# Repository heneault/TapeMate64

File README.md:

# TapeMate64 - Connect your Commodore Datasette to a PC

**TapeMate64** is a compact and affordable USB adapter that lets you connect a **Commodore Datasette** to your PC via **USB** for both reading and writing cassette data. It enables you to **digitize original tapes** for archiving or for use in an emulator—without needing a working Commodore 64.

It also allows you to **write TAP images back to real cassette tapes**, so you can enjoy software on original hardware for the full retro experience.

---

## 📺 Project Presentation
Watch the full presentation and live demo of **TapeMate64** at the **TPUG (Toronto PET Users Group)** meeting (December 2025):

👉 **[TapeMate64 Presentation at TPUG - Watch on YouTube](https://youtu.be/ml87w1ATcyY?si=blFYjihloHmHbtkc)**

---

Based on the [TapeBuddy64](https://github.com/wagiminator/C64-Collection/tree/master/C64_TapeBuddy64) project, TapeMate64 adds a builder-friendly design. You can operate it via a command-line interface or a Python-based graphical front-end.

The main differences of TapeMate64 over the original TapeBuddy64 project are:

* It uses readily available and popular modules that are easy to order online, such as the **Arduino Nano Super Mini** and the **MT3608** boost converter.
* All modules and components are soldered using **Through-Hole Technology (THT)**, which is much simpler to solder than Surface-Mount Device (SMD) components.
* The original TapeBuddy code was **ported to the ATmega** microcontroller used by the Arduino board, which is a much more common CPU than the original.
* The software was also modified to provide **better precision** for long and short pulses.
* Enhanced CRC computation has been added for improved data integrity.
* The applications (GUI and command-line) are precompiled and ready to use, so there is no need to install Python.
* No switch is required for programming or operation, everything is handled automatically.
* Additional special-case handling was implemented, particularly for tape-writing operations.

__
__

---

# Where to Order a Kit

I will have some kits for sale at the [World of Commodore](https://woc.tpug.ca/) event, organized by **TPUG**, during the weekend of **December 6-7, 2025**. Any remaining kits will be sold online after the event.

---

# Instructions to Assemble the Board

To properly build and calibrate your TapeMate64, please follow the steps in the [build instructions](build_guide/BUILD.md). **Carefully adjusting the MT3608 is very important** to avoid damaging your Datasette.

---

# Firmware and Application Download Release

The latest application release can be [downloaded here](https://github.com/heneault/TapeMate64/releases/latest). Download the zip file corresponding to your operating system (**Windows or Linux**). Extract the entire zip file to access the different applications.

## Installing Windows Driver

Windows users may need to install a [driver](https://www.wch-ic.com/downloads/ch341ser_exe.html) for the **CH340N USB-to-serial adapter**. If the application does not detect the board, install the driver, reboot your PC, and try again.

## Uploading the Firmware

* Connect the device to a **USB port** on your PC.
* Use one of the following methods:

### If using the Graphical Front End (Recommended)

* Execute the following command on your PC: `tape-gui.exe`.
* Click on **<kbd>Flash firmware</kbd>**.

### If using the Command Line Tool

* Execute the following command on your PC: `flash-firmware.exe`.

---

# Operating Instructions

## Preparation

* Connect your **TapeMate64** to your **Commodore Datasette**.
* Connect your **TapeMate64** to a **USB port** on your PC.
* Ensure that you have properly flashed the firmware.
* Safety Note: Always disconnect from the **USB port** before unplugging the **Commodore Datasette**.

## Command Line Interface

The following command-line tools are available:

### Reading from Tape

* Execute the following command on your PC: `tape-read.exe outputfile.tap`.
* Press **<kbd>PLAY</kbd>** on your Datasette when prompted.
* The dumping process is **fully automatic**. It stops when the end of the cassette is reached, when no more signal is detected on the tape for a certain period, or when the **<kbd>STOP</kbd>** button on the Datasette is pressed.

### Writing on Tape

* Execute the following command on your PC: `tape-write.exe inputfile.tap`.
* Press **<kbd>RECORD</kbd>** on your Datasette when prompted.
* The recording process is **fully automatic**. It stops when all data has been written, the end of the cassette is reached, or when the **<kbd>STOP</kbd>** button on the Datasette is pressed.

## Graphical User Interface

* Execute the command on your PC: `tape-gui.exe`.
* The rest of the operation should be self-explanatory.

## Status LEDs

|LED|Description|
|:-|:-|
|**Blue**|**Steady:** Device is powered via USB.|
|**Green**|**Steady:** Device is reading from the tape.<br>**Flashing:** Device waits for the **<kbd>PLAY</kbd>** or **<kbd>STOP</kbd>** button to be pressed.|
|**Red**|**Steady:** Device is writing to the tape.<br>**Flashing:** Device waits for the **<kbd>RECORD</kbd>** or **<kbd>STOP</kbd>** button to be pressed.|

## Troubleshooting Tips

If you experience **buffer underrun or overrun** errors, especially on Windows, please check the following:

* **Windows is not a real-time OS**, so if another process preempts the application for too long, the serial port transfer can fail.
* **Antivirus:** Make sure your antivirus software is not running a scan.
* **Screen Saver:** Disable any screen saver that could consume too much CPU.
* **Other Applications:** Do not run any other demanding applications simultaneously.
* **CPU Usage:** Monitor your CPU usage using the Task Manager (it should be relatively low if nothing else is running).
* **Administrator Mode:** Try running the application in administrator mode. You can do this by right-clicking the application's shortcut and selecting **"Run as administrator,"** or by opening a command shell (search for "cmd," then right-click on "Command Prompt" and select "Run as administrator"), navigating to the application's folder, and launching it manually.
* **Older Computers:** On older computers, the command-line tools are sometimes more suitable than the GUI.

---

# Hardware Description

The schematic is shown below:

## Microcontroller

The heart of the system is an **Arduino Nano Super Mini**. This board is similar to a classic Arduino Nano but has a smaller footprint and includes onboard LEDs. It's a very popular board and includes the necessary voltage regulator and USB-to-serial chip, making it an excellent choice for this project. The USB port is used both for **flashing the firmware** and for **operating the device**. The microcontroller on the board is a widely supported **ATmega328**.

## Booster Converter

The **MT3608 boost converter** is used to provide the approximately **6 Volts** required for the Datasette's motor. The ATmega can switch the motor on and off via an optocoupler and a transistor when a key press is detected on the Datasette.

## Cassette Port

The cassette port is a **6-pin edge connector** integrated into the printed circuit board (PCB) with a **3.96mm** spacing. The Datasette's connector plugs directly onto this port. A notch between pins B/2 and C/3 prevents accidental polarity reversal.

|Pin|Signal|Description|
|:-|:-|:-|
|**A / 1**|GND|Ground|
|**B / 2**|+5V|5 Volt DC|
|**C / 3**|MOTOR|Motor Control, approx. 6 Volt power supply for the motor.|
|**D / 4**|READ|Data Input, read data from the Datasette.|
|**E / 5**|WRITE|Data Output, write data to the Datasette.|
|**F / 6**|SENSE|Detection, senses if one of the **<kbd>PLAY</kbd>**, **<kbd>RECORD</kbd>**, **<kbd>F.FWD</kbd>**, or **<kbd>REW</kbd>** keys is pressed.|

---

# Software

## Working Principle

Data is stored on the tape as a **frequency-modulated waveform**. This signal is read from the Datasette, amplified, converted into a **TTL-level square wave** with the same pulse lengths, and then output to the cassette port's **READ pin**. TapeMate64 reads this square wave and measures the **pulse durations** between the signal's falling edges. These pulse lengths are then sent to the PC via USB and written into the **TAP file** in the correct format after being adjusted using the clock frequency.

Writing to tape works in the opposite way. TapeMate64 generates a square wave with the corresponding pulse lengths based on the TAP data values (the signal is inverted when writing) and sends it through the **WRITE pin** to the Datasette, which then generates the corresponding waveform and records it onto the cassette.

## Interpretation of the Pulse Lengths

The actual data is encoded using a sequence of pulses of different lengths. The standard Commodore system uses patterns of three different pulse lengths: **short** ($390\mu\text{s}$), **medium** ($536\mu\text{s}$), and **long** ($698\mu\text{s}$).

* Each data byte is preceded by a **marker** consisting of a long pulse followed by a medium one.
* A **"0" bit** is represented by a short pulse followed by a medium one.
* A **"1" bit** is a medium pulse followed by a short one.
* Each byte on the tape ends with a **parity bit**.
* Combinations of long pulses with medium or short pulses are used as a byte marker or end-of-data marker.

However, **fast loaders** are often used, and each one uses different pulse lengths and patterns, which complicates the overall decoding. Fortunately, TapeMate64 does not need to decode the data. This is because **only the raw data**—the individual pulse lengths—is saved in the TAP file. The actual interpretation of these pulses is handled later by the C64 or a corresponding emulator.

## Timing Accuracy

The accuracy of the pulse lengths depends on various factors. For instance, not all motors in Datasettes run at exactly the same speed. Additionally, the C64 measures the pulse length via the CIA timer as the number of elapsed system clock cycles, but **PAL versions of the C64** have a different clock frequency ($985248 \text{ Hz}$) than **NTSC versions** ($1022730 \text{ Hz}$). Furthermore, badly aligned Datasette heads and old tapes with weakened signals also contribute to potential timing variations.

For these reasons, the difference between the individual pulse lengths used for data encoding is large enough to be reliably distinguished even under the circumstances mentioned. In fact, what matters is not the measured pulse length itself, but whether it is **above or below a defined threshold value**. Moreover, turbo loaders often employ a mechanism to synchronize with the data stream from the Datasette.

## TAP File Format

The **TAP file format** attempts to duplicate the data stored on a C64 cassette tape, bit for bit. It was designed by Per Håkan Sundell (author of the [CCS64](http://www.ccs64.com/) C64 emulator) in 1997. Since it is simply a representation of the raw serial data from a tape, it should be able to handle any custom tape loaders that exist. The layout is fairly simple, with a small **20-byte header** followed by the file data:

|Bytes (hex)|Description|
|:-|:-|
|0000-000B|File signature **"C64-TAPE-RAW"**|
|000C|TAP version (**0** - original, **1** - updated, **2** - halfwave extension)|
|000D|Computer platform (**0** - C64, **1** - VIC-20, **2** - C16, Plus/4, **3** - PET)|
|000E|Video standard (**0** - PAL, **1** - NTSC, **2** - OLD NTSC, **3** - PALN)|
|000F|Future expansion|
|0010-0013|File data size (**little endian**; not including the header)|
|0014-xxxx|File data|

In **TAP version 0**, each data byte in the file data area represents the length of a single pulse, determined by the following formula:
$$\text{data byte} = \frac{\text{pulse length (in seconds)} \times \text{C64 clock frequency (in Hertz)}}{8}$$

Therefore, the data value for a pulse length of $390\mu\text{s}$ would be:
$$0.000390\text{s} \times 985248\text{Hz} / 8 \approx 48 \quad (0\text{x}30 \text{ in hex})$$

A data value of **$0\text{x}00$** represents an **"overflow"** condition—any pulse length greater than $255 \times 8$ clock cycles (or $2078\mu\text{s}$). Such a pulse length does not encode any data and typically only occurs in the pauses between programs on the same tape. However, the lengths of these pauses can be relevant for some fast loaders.

In **TAP version 1**, the data value of **$0\text{x}00$** was re-coded to represent values greater than $255 \times 8$ clock cycles, or to provide a greater resolution (one clock cycle instead of eight). When a $0\text{x}00$ is encountered, it is followed by **three bytes** that represent the actual pulse length in C64 clock cycles. These three bytes are stored in **little-endian format** (least significant byte first). For example, a data value for a pulse length of $2875\mu\text{s}$ would be:
$$0.002875\text{s} \times 985248\text{Hz} \approx 2832 \quad (\text{data bytes: } 0\text{x}00, 0\text{x}10, 0\text{x}0\text{B}, 0\text{x}00)$$

**TAP Version 2** is an extension made by Markus Brenner for C16 tapes. It is based on Version 1, but each value represents a **halfwave**, starting with a '0' to '1' transition. The time encoding remains the same.

TapeMate64 can **read TAP versions 0 and 1** and **write them to cassette**. It uses **TAP version 1** to generate a TAP file when reading from the Datasette. The pauses between individual files on the tape are also precisely recorded, ensuring the device should be able to handle all types of fast loaders.

## Software Implementation

### Serial Interface

The Python scripts on the PC control the device via four simple serial commands:

|Command|Function|Response|
|:-:|:-|:-|
|**"i"**|Transmit identification string|**"TapeMate64\n"**|
|**"v"**|Transmit firmware version number|e.g. **"v1.0\n"**|
|**"r"**|Read file from tape|Send raw data stream|
|**"w"**|Write file on tape|Receive raw data stream|

### Reading from Tape

The ATmega measures the pulse lengths using its **Timer 1**.

1.  The timer counts continuously upwards at **2 MHz** until a **falling edge** is detected at the Datasette's READ output, or until a **timer overflow** occurs. A frequency of 2 MHz provides very good precision for reading the pulse.
2.  An **overflow interrupt** occurs every $32.768 \text{ ms}$ if no falling edge interrupt is detected. Overflows are accumulated until the falling edge interrupt occurs or a stop/timeout condition is met.
3.  When the falling edge occurs, the timer counter value is automatically added to any accumulated overflow.
4.  The final count is then **divided by 2** to adjust the value to the number of **microseconds**. This value is placed into a buffer queue to be sent to the PC. The timer counter and overflow are then reset to zero, and the process restarts.
5.  While there are no interrupts, the main program sends the value from the queue to the PC via the serial-to-USB port.
6.  Values are encoded as the number of microseconds using **3 bytes**.
7.  The raw data stream begins with a **$0\text{x}00$** as soon as **<kbd>PLAY</kbd>** on the tape is pressed.
8.  Pulse lengths shorter than $8\mu\text{s}$ are ignored.
9.  If **<kbd>STOP</kbd>** is pressed or a timeout occurs while waiting for valid pulses, the end of the stream is indicated by a **$0\text{x}000000$** word.
10. Afterwards, the **16-bit checksum** (calculated using CRC-16 of all data bytes) is transmitted.
11. Finally, the **tape buffer overflow flag** is transmitted as a single byte ($0\text{x}00$ means no overflow occurred).
12. If **<kbd>PLAY</kbd>** was not pressed within the defined initial period, a **$0\text{x}01$** is sent instead of $0\text{x}00$, and the procedure is terminated.

The Python script writes the TAP file header, converts the received data words into the corresponding TAP values, and writes them to the output file.

### Writing on Tape

1.  The Python script on the PC opens the TAP file and validates it.
2.  It converts all data from the TAP file into the corresponding **24-bit words** for transmission to the TapeMate64 and stores them in a temporary file.
3.  The script then sends the write command **"w"** to the TapeMate64.
4.  After receiving a **$0\text{x}00$** byte from the TapeMate64, which indicates that **<kbd>RECORD</kbd>** was pressed, the PC starts to send the first data packet after it is requested by the TapeMate64.
5.  The TapeMate64 temporarily stores the received data in a buffer. As soon as the buffer level drops below a certain point, it requests new data from the PC by sending a byte that indicates the number of values requested in the next packet.
6.  The ATmega uses its **Timer 1** to output a signal with a **50% duty cycle** by default at the cassette port's WRITE pin. Since Timer 1 runs at $2 \text{ MHz}$ and values are sent from the PC aligned to microseconds, the same value can be used for each half of the period to program the timer.
7.  When the timer interrupt is triggered, the handler first verifies whether it should create the **first or second half** of the cycle. After a full period, it continues with the next value from the buffer queue.
8.  If a value has a period longer than the maximum timer period ($32.768 \text{ ms}$), the timer is programmed with this maximum value, and bookkeeping is done to track the remaining period. On the next interrupt, the remaining period value is decremented until the timer has fully completed the cycle. This creates a very precise, **pulse-length modulated square wave**.
9.  If there is no more data in the TAP file, the Python script sends a **$0\text{x}000000$** word to indicate the end of the transfer.
10. TapeMate64 then sends back a **$0\text{x}00$** byte as soon as all data in the buffer has been output as pulses.
11. Finally, the **16-bit CRC16 checksum**, the **buffer underrun flag**, and the current status of the **<kbd>RECORD</kbd>** key are transferred to the PC. The Python script checks these values and reports whether the recording was successful.

### Addressing Writing Issues

**Long Pulses and Duty Cycle:** Very long pulses can sometimes cause the Datasette to misinterpret the signal. If we use a fixed 50% duty cycle, the signal will remain too long during the first half of a long pulse. This cause the Datasette's internal electronics to prematurely detect the pulse's edge and switch to the second half of the cycle, leading to recording errors (false pulses).

To avoid this, the implementation briefly adjusts the duty cycle at the beginning of a long pulse. It first quickly performs the required edge transition by outputting a very short pulse of the opposite polarity. After this quick transition, it holds the output steady for the remaining duration of the long pulse. This approach ensures a clean, sharp edge at the start of the pulse, preventing glitches or false triggers on the tape and guaranteeing reliable timing.

**Timer Interrupt Conflicts:** Another potential issue during writing occurs when a pulse period is slightly longer than the timer's maximum representable value. The timer would first wait for its maximum period, then wait for a very small remainder. If this remainder is too close to zero, the interrupt handler may not have enough time to react. The compare register could immediately re-trigger the interrupt while the current interrupt is still being processed. This results in the timer running past the intended point, overflowing to zero, continuing to count, and eventually triggering the interrupt much later than expected—producing an unintended, very long pulse. To prevent this, the code splits any pulse period that slightly exceeds the timer’s limit into two roughly equal halves. This guarantees that each timer period is long enough for the interrupt handler to run reliably and avoids spurious long pulses.

## Compiling the Firmware (For Developers)

Follow these steps to compile the firmware yourself:

1.  Visit [https://code.visualstudio.com/](https://code.visualstudio.com/).
2.  Download the installer for your operating system (Windows, macOS, or Linux).
3.  Run the installer and accept the default options.
4.  When the installation is complete, open **Visual Studio Code**.
5.  In VS Code, click the **Extensions** icon on the left sidebar (the four squares).
6.  In the search bar, type **PlatformIO IDE**.
7.  Click **Install** on the extension published by *PlatformIO Labs*.
8.  Wait for the installation to finish, then click **Reload Now** when prompted.
9.  You should now see the **PlatformIO (ant head)** icon in the left sidebar.
10. Select the folder containing the AVR project (`TapeMate64/software/avr`).
11. VS Code automatically recognizes it as a PlatformIO project.
12. The **PlatformIO Toolbar** appears at the bottom of the window (with **✓ Build**, **→ Upload**, and **Plug** icons).
13. PlatformIO will automatically install the necessary toolchains and libraries as defined in the `platformio.ini` file.
14. Click the **✓ Build** icon in the PlatformIO toolbar.
15. Watch the output panel for progress and errors.
16. When the process reports **“SUCCESS”**, your firmware has been compiled successfully and saved under `.pio/build/nanoatmega328/`.
17. Plug your board into your computer via USB.
18. Wait a few seconds for PlatformIO to detect it.
19. At the bottom bar, click the **PlatformIO: Devices** (plug) icon.
20. Note or select the correct serial port (e.g., `COM3` on Windows or `/dev/ttyUSB0` on Linux/macOS).
21. Click the **→ Upload** icon in the PlatformIO toolbar.
22. PlatformIO will compile (if needed) and then upload your program to the board.
23. When you see **“Uploading done”**, the process is complete.

## Installing Python for Application Development

If you want to modify the application running on the computer, you need to have **Python** installed on your PC. Most Linux distributions already include this. Windows users can follow these [instructions](https://www.pythontutorial.net/getting-started/install-python/).

You should also create a **virtual environment** to install the required dependencies, following these steps:

1.  Open a terminal and move into the project folder:
    `cd TapeMate64/software/pc`
2.  Create the virtual environment (`venv`):
    `python3 -m venv venv`
3.  Activate the virtual environment:
    `source venv/bin/activate`
4.  Install the requirements:
    `pip install -r requirements.txt`

## Checking, Cleaning, and Converting TAP Files

The TAP files generated by TapeMate64 can be used directly in your favorite emulator, but you might want to check, optimize, or convert them beforehand. This works perfectly with the command-line tool **[TAPClean](https://sourceforge.net/projects/tapclean/)**.

* **To check the quality** of the generated TAP image, use the following command:
    `tapclean -t outputfile.tap`
    *Remember that a TAP file is almost never 100% clean, as pauses in particular are not always correctly recognized.*
* **You can optimize the quality** of the file with the following command:
    `tapclean -o outputfile.tap`
    *This compensates for slight deviations in the pulse lengths and adapts everything to the exact timing specifications. TAPClean knows the required pulse lengths not only for the standard Commodore coding but also for all common fast loaders.*
* **If you want to convert the TAP file into a WAV audio file**, use the following command:
    `tapclean -wav outputfile.tap`

There is also a graphical [front end](https://www.luigidifraia.com/software/) available for TAPClean.

## Datasette Head Alignment

If you have trouble loading programs from tape, the **azimuth of the tape head** may be out of position. Before adjusting the azimuth, however, you should rule out all other causes of error:

1.  Try other cassettes first, as tapes will age over time and the signals will weaken.
2.  Clean the connector contacts with contact cleaner.
3.  Clean the read head with isopropyl alcohol.

If it still doesn't work, it's time for the screwdriver.

To adjust the azimuth, there is a tiny screw hole above the rewind button through which a small jeweler's screwdriver can fit. When the tape drive is playing, the hole will align with the head adjustment screw. **Do not apply too much pressure and avoid over-tightening or over-loosening the screw!**

Follow these steps:

1.  Insert a cassette into the Datasette that you know is working well.
2.  Execute `tape-gui.exe`.
3.  Select "Read from tape to TAP file," then select the output file (you can delete it later).
4.  Press **<kbd>PLAY</kbd>** on the Datasette when prompted.
5.  As soon as the pulse lines are displayed, take a thin screwdriver and **slowly adjust the azimuth until the displayed lines are as narrow as possible**.

---

# References, Links and Notes

1.  [TapeBuddy64](https://github.com/wagiminator/C64-Collection/tree/master/C64_TapeBuddy64)
2.  [TrueTape64 Project](https://github.com/francescovannini/truetape64)
3.  [How Commodore Tapes Work](https://wav-prg.sourceforge.io/tape.html)
4.  [How TurboTape Works](https://www.atarimagazines.com/compute/issue57/turbotape.html)
5.  [Analyzing C64 Tape Loaders](https://github.com/binaryfields/zinc64/blob/master/doc/Analyzing%20C64%20tape%20loaders.txt)
6.  [Archiving C64 Tapes Correctly](https://www.pagetable.com/?p=1002)
7.  [TAP File Format](https://ist.uwaterloo.ca/~schepers/formats/TAP.TXT)
8.  [VICE Emulator File Formats](https://vice-emu.sourceforge.io/vice_17.html)
9.  [TAPClean](https://sourceforge.net/projects/tapclean/)
10. [TAPClean Front End](https://www.luigidifraia.com/software/)
11. [Datasette Service Manual](https://www.vic-20.it/wp-content/uploads/C2N-1530-1531-service_manual.pdf)
12. [Adjusting the Datassette Head Azimuth](https://theokoulis.com/index.php/2020/11/15/some-notes-on-adjusting-the-datassette-head-azimuth-on-the-vic-20/)
13. [ATmega Datasheet](https://ww1.microchip.com/downloads/aemDocuments/documents/MCU08/ProductDocuments/DataSheets/ATmega48A-PA-88A-PA-168A-PA-328-P-DS-DS40002061B.pdf)
14. [MT3608 Datasheet](https://components101.com/sites/default/files/component_datasheet/MT3608-Step-Up-Power-Module-Datasheet.pdf)
15. [Arduino Nano Super Mini](https://github.com/maltman23/ArduinoNanoSuperMini)

---

# License

This work is licensed under the Creative Commons Attribution-ShareAlike 3.0 Unported License.
(http://creativecommons.org/licenses/by-sa/3.0/)

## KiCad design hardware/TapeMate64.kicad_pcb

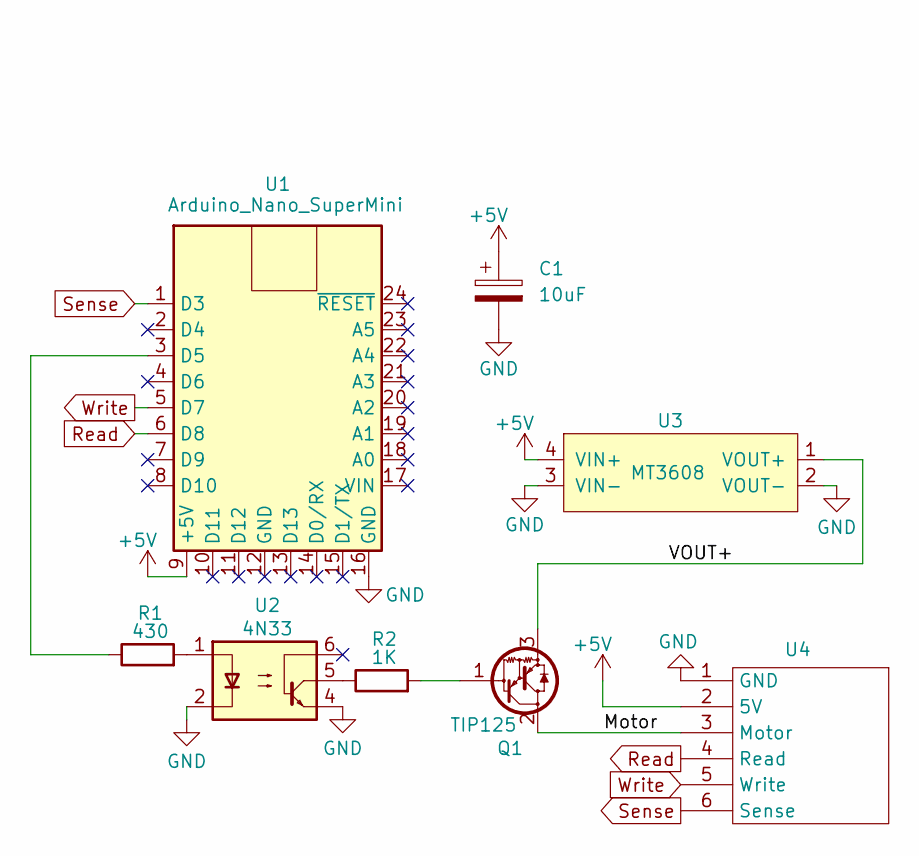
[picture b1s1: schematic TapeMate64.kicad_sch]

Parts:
C1: 10uF; CP_Axial_L11.0mm_D5.0mm_P18.00mm_Horizontal
Q1: TIP125; TO-220-3_Vertical
R1: 430; R_Axial_DIN0204_L3.6mm_D1.6mm_P7.62mm_Horizontal
R2: 1K; R_Axial_DIN0204_L3.6mm_D1.6mm_P7.62mm_Horizontal
U1: Arduino_Nano_SuperMini; Nano_V3_SuperMini
U2: 4N33; DIP-6_W7.62mm
U3: MT3608
U4: EDGE_CON_12P_TAPE

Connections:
+5V: C1.1, U1.9 (+5V), U3.4 (VIN+), U4.2 (5V)
/Motor: Q1.2 (C), U4.3 (Motor)
/VOUT+: Q1.3 (E), U3.1 (VOUT+)
GND: C1.2, U1.16 (GND), U2.2, U2.4, U3.2 (VOUT-), U3.3 (VIN-), U4.1 (GND)
unnamed: Q1.1 (B), R2.2
unnamed: R1.2, U2.1
unnamed: R2.1, U2.5
unnamed: R1.1, U1.3 (D5)
Read: U1.6 (D8), U4.4 (Read)
Sense: U1.1 (D3), U4.6 (Sense)
Write: U1.5 (D7), U4.5 (Write)

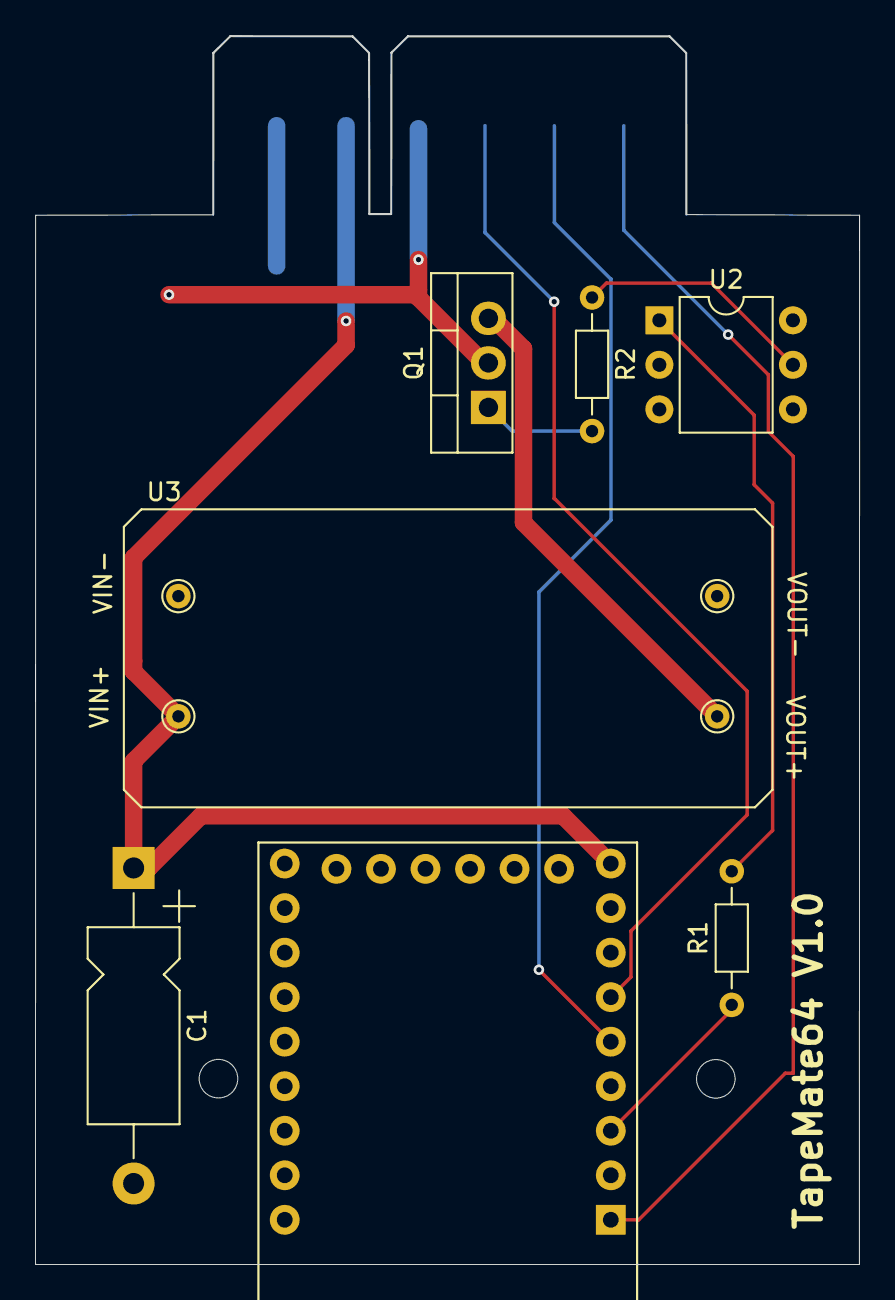
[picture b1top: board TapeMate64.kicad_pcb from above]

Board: 2 copper layers, 47.0 x 70.1 mm, 8 parts (1 on the bottom side), 11 nets.

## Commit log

2025-11-21 updated link to release
2026-03-13 adjusted front pulse hack timing
2026-03-13 updated to version 1.0.1
2026-03-13 update branch name in workflow
2026-03-17 adjusted long timer value
2026-03-17 updated firmware
2026-03-22 Update README.md with a safety note
2026-03-28 added link to youtube video

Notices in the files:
README.md:
License:
This work is licensed under the Creative Commons Attribution-ShareAlike 3.0 Unported License.
(http://creativecommons.org/licenses/by-sa/3.0/)
